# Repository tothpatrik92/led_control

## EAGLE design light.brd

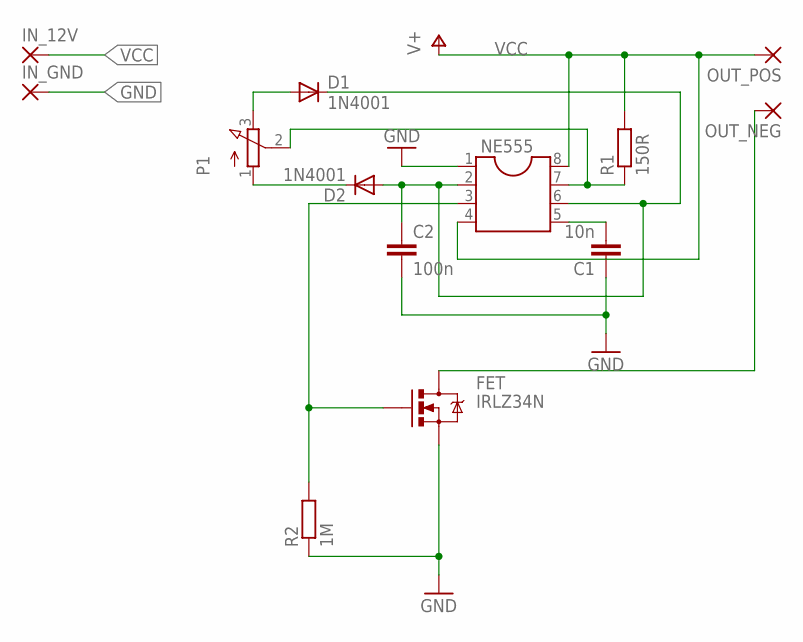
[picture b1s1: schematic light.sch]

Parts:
C1: 10n; C025-024X044
C2: 100n; C025-024X044
D1, D2: 1N4001; DO41-10
FET: IRLZ34N; TO-220(2)
IN_12V: 3,81/1,3
IN_GND: 3,81/1,3
NE555: DIL8; DIL08
OUT_NEG: 3,81/1,1
OUT_POS: 3,81/1,1
P1: 3RP/1610N
R1: 150R; 0207/7
R2: 1M; 0207/7

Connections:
GND: C1.1, C2.2, FET.OUT (S), IN_GND.1, NE555.1, R2.1
unnamed: D2.C, P1.1 (A)
unnamed: NE555.7, P1.2 (S), R1.1
unnamed: D1.A, P1.3 (E)
unnamed: C1.2, NE555.5
unnamed: FET.IN (G), NE555.3, R2.2
unnamed: FET.GND (D), OUT_NEG.1
unnamed: C2.1, D1.C, D2.A, NE555.2, NE555.6
VCC: IN_12V.1, NE555.4, NE555.8, OUT_POS.1, R1.2

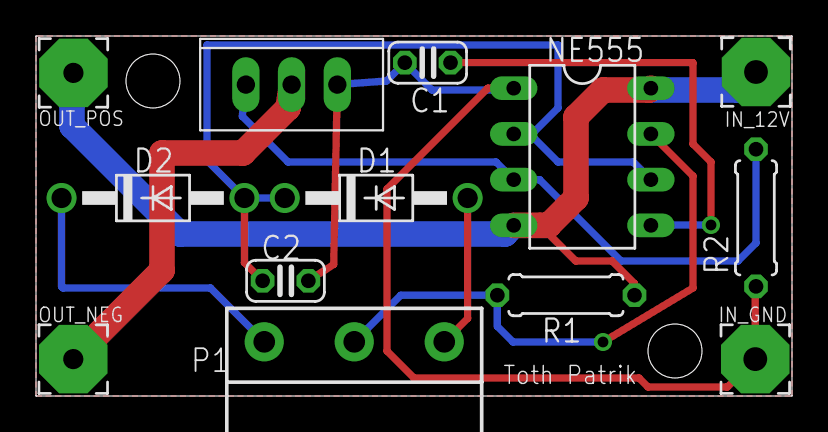
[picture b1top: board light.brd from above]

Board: 2 copper layers, 42.0 x 20.0 mm, 13 parts (0 on the bottom side), 9 nets.

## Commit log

2020-10-18 LED control
